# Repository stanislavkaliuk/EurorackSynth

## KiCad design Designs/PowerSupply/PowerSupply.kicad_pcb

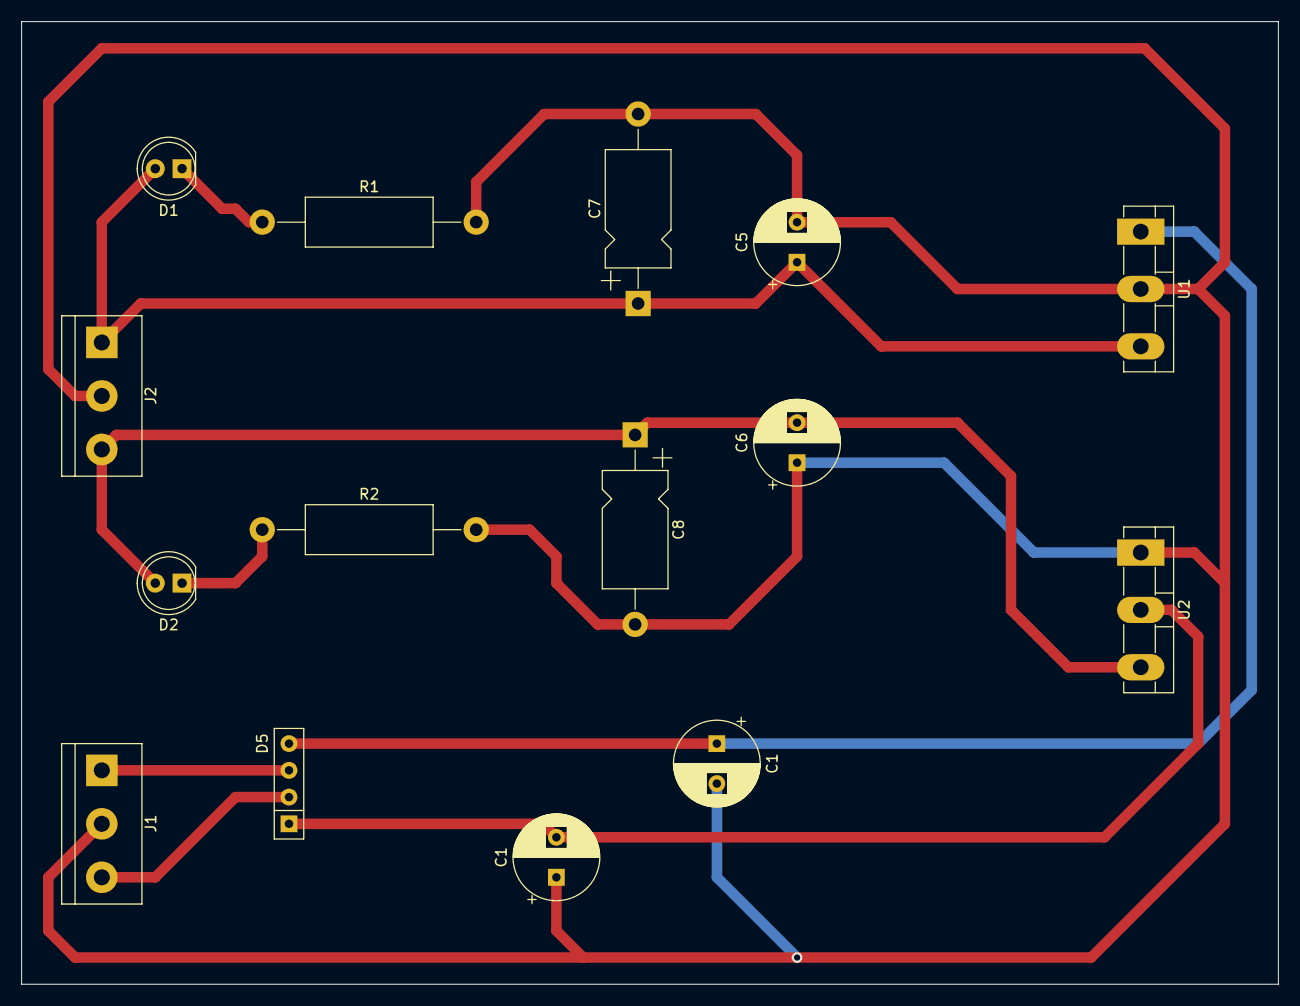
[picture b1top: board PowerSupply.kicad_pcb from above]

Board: 2 copper layers, 119.4 x 91.4 mm, 15 parts (0 on the bottom side), 9 nets.

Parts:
C1, C1#2: 2200uf/35V; CP_Radial_D8.0mm_P3.80mm
C5, C6: 100uf/35V; CP_Radial_D8.0mm_P3.80mm
C7, C8: 0.1uf; CP_Axial_L11.0mm_D6.0mm_P18.00mm_Horizontal
D1, D2: LED; LED_D5.0mm
D5: D_Bridge_-AA+_RS207_2A; R_Array_SIP4
J1: In; TerminalBlock_bornier-3_P5.08mm
J2: Out; TerminalBlock_bornier-3_P5.08mm
R1, R2: 2.2K; R_Axial_DIN0414_L11.9mm_D4.5mm_P20.32mm_Horizontal
U1: L7812; TO-3P-3_Vertical
U2: L7912; TO-3P-3_Vertical

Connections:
GND: C1.2, C1#2.1, C5.2, C6.1, C7.2, C8.2, J1.2, J2.2, R1.2, R2.2, U1.2 (GND), U2.1 (GND)
unnamed: C5.1, C7.1, D1.2 (A), J2.1, U1.3 (OUT)
unnamed: D1.1 (K), R1.1
unnamed: D2.1 (K), R2.1
unnamed: C6.2, C8.1, D2.2 (A), J2.3, U2.3 (VO)
unnamed: C1.1, D5.4 (+), U1.1 (IN)
unnamed: C1#2.2, D5.1 (-), U2.2 (VI)
unnamed: D5.3, J1.1
unnamed: D5.2, J1.3

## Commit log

2023-02-21 PowerSupply schematic and pcb prototype
2023-02-26 update powersupply design
2023-02-26 add vco design without jacks'
